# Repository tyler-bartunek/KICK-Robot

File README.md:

# The KICK Robot 

&nbsp;
&nbsp;
_Democratizing robotics, one shoebox at a time_

The KICK (Kinematically Interchangeable Control Kit) Robot framework is an open-source platform designed to make learning about and development of mobile robotic systems accessible, modular, and affordable.

## Table of Contents
- [Repository Structure](#repository-structure)
- [The Wiki](#the-wiki)
- [Module Descriptions](#module-descriptions)
- [Hardware](#hardware)
  - [Printed Components and Module Fit](#printed-components-and-module-fit)
- [Future development](#future-development)
- [FAQ](#faq)
- [License](#license)

## Repository Structure
- `/hardware/` – STL and STEP files for 3D printing
- `/software/` – Code for the centralized controller (in progress), example firmware for modules, and hardware test scripts
- `/docs/` – Printing instructions, and additional reference material as it becomes available (PDF)
- `/images/` – Holds images used in this README, as well as some others throughout the repository
- `README.md` – You are here.

## The Wiki
Documentation for this project, including: 

- Part orientation and printer setting recommendations
- Assembly instructions
- Calibration and hardware validation protocols
- System-level descriptions
- and more

are being migrated to the [project wiki](https://www.github.com/tyler-bartunek/KICK-Robot/wiki) for ease of access
and navigation purposes. There's a lot that goes into this system, and it is only fitting that worthy documentation
would be quite extensive, requiring a wiki to track it all. 

## Module Descriptions
Here are a few of the modules under development at present for the KICK Robot. Once these modules are fully fleshed
out, a homebrew guide will be produced and added to the wiki.

1. Wheels: This module consists of DC motors and mecanum wheels, represents minimal functional example (systems integration in process).
2. Shoeshine: Offers quadrupedal motion through use of servomotors (Pending Initial Design)
3. HexaBox: Requires six mounts, offers six-legged locomotion through use of servomotors. (Pending Initial Design)

Note that each module type gets its own uint8_t identifier. Here are some urrently used ID's within KICK framework:

| ID | Module Type |
|----|-------------|
|0x00 | **Reserved**: No Connection |
|0x01 | Echo test functionality |
|0x02 | Mecanum Wheel Version A |
|0x03 | Mecanum Wheel Version B |
|0x04 | Quadruped Leg Version A |
|0x05 | Quadruped Leg Version B |

## Hardware

### Printed Components and Module Fit
Both STEP and STL files for all components to be printed are provided under the hardware directory, with directions for
the base hardware and wheels module provided in the wiki. As modules are added, printing directions specific
to those modules will be added. This system was prototyped using an Ender 3 V2 and Cura slicer using 
PLA+, with dimensions set to reflect typical tolerances for that printer with the intent of clearance fits with minimal play between 
mounting rails and modules.

## Software
Files for characterizing your specific motors and verifying basic hardware connections to the Pi, such as the ADC for 
battery level monitoring and custom SPI fanout board PCB, are provided within this repository, as well as the base
code for the picos/modules. Module code was developed using the Raspberry Pi Pico C++ SDK and uses CMake (C++17).

ROS code for the Raspberry Pi was developed using the ros:jazzy-core docker image, and is available on a [separate repository](https://github.com/tyler-bartunek/kick_pi) for direct download on your raspberry pi once finished. Raspberry 3b+ or better strongly encouraged, as the project was developed on a 3b+. 

### Philosophy, Parent Classes: Validation Ongoing, wiki articles available upon completion
While this is explained in greater detail in the [wiki](https://www.github.com/tyler-bartunek/KICK-Robot/wiki), provided here is a brief overview
for integration purposes. Overall, the goal is for users to be able to extend this framework to arbitrary module configurations. 

#### Configuration Class (ROS)
Within this project's underlay (not to be confused with the ROS underlay), there is a kickbrain package. This package has a nested package within it
called "configuration_files". The Configuration class is defined within this subpackage, and all kinematic calculations are predicated on the geometry_msgs.msg.Twist message type coming from the motion planner, with these velocities defined relative to the center of mass, presumed or actual. 

**All user-defined configurations must inherit from the Configuration parent class and have both a fetch_commands and compute_received method defined as following signatures:** 
```
def fetch_commands(self, vel_cmd: Twist, feedback) -> list:
```

This method takes the center of mass velocity command from the motion planning node, which uses the built-in geometry\_msgs.Twist topic message type and any feedback to compute new actuator commands. 

``` 
def compute_received(self, device_data) -> Twist:
```
This method takes the data received from the bus\_hub node and computes the forward kinematics for your configuration to build feedback. 

Once you have your configuration kinematics defined, you go to the \_\_init\_\_.py file within the configuration\_files directory and add the frozenset of module ids that can be used to recognize your configuration. Note that it does use a frozenset, so if you need X number of modules for a successful deployment, be sure to add that check to your custom configuration's class definition.

__**Note that 0x00 is reserved as the "no connection" module ID, so your frozenset will need to include it if any connection points on the harness are disconnected**__

_There is a possibility that you will need to modify it directly within the kickbot_node package and rebuild it using colcon build --packages-select to achieve desired behavior, but efforts will be made to allow you to develop your own configuration definitions in an overlay._

#### Module Class (Pico)
The microcontroller code for the picos is organized in the following folder structure:

1. kick_pico: **project root, make/build from here** <br>
   a. modules: Contains the Module parent class and any subclass definition cpp and h files <br>
   b. utils: Additional cpp and header files for achieving any functionality the modules require, such as SPI communication or quadrature encoder reading <br>
   c. main.cpp: driver script, creates the `pico_device` instance and calls its `run()` method repeatedly <br>

You define your custom module by adding a header and cpp file within the modules subdirectory, and be sure to add the relevant files to the CMakeLists.txt file within that subdirectory. The custom module class that you define **must** inherit from the Module base class, and must include a run method override that defines your module's behavior in response to received data from the Pi. That run method **must** call `this -> Transfer(data)`, where `data` is a short (uint16\_t) being sent back to the pi. 

Minimally viable example of a custom subclass header file:
```
#pragma once

#include "Module.h"

class MinimalExample : public Module {
    
    public:
        
        MinimalExample();

        void run() override;

        ~MinimalExample() = default;
};
```

If your module requires additional custom header files to function, these go under the utils subdirectory and you will in turn need to modify that CMakeLists.txt file.

For example, if you need to add something for the module to read an encoder that you've either written or cloned a library for named MyReallyCoolEncLib, you would modify the very first line of CMakeLists.txt file in utils to read:

```
add_library(utils STATIC SPITools.cpp MyReallyCoolEncLib.cpp)
```

assuming that your library has a cpp file defined for it.

Lastly, you modify line 18 of main.cpp to have the name of your new module type

```
#define MODULE_TYPE MinimalExample
```

**When you define your own module definitions they must inherit from the Module base class, have a unique uint8_t ID defined, and contain a run() method override.** A sync_callback() method override is optional, but recommended if the modules need to act in a coordinated fashion (as most do). Wiki article coming soon.  

## Future development
This project is still under development, and additional details such as synchronization and timing
requirements will be made available as they are validated. Current work is focused on validating the ROS setup and getting the Wheels Module ready to ``roll". 

## FAQ

1. Why shoeboxes?

>I had originally set out to make what essentially amounts to just the wheels module as a CAD and mechatronic portfolio piece.
Seeking to understand the design considerations, I started to immerse myself in literature surrounding mecanum wheel devices 
and discovered something that is in hindsight self-evident: different design decisions like the wheel spacing and orientation 
fundamentally alters the dynamics of the system and therefore influence control. Creating modular systems to explore the impact 
of these parameters was largely underexplored in what I found, so I set out to make my own. But I needed a good frame. Something
cheap and easy to deploy. As I looked around me, I saw an unused shoebox. And the KICK Robot was born. 

>Realistically any cardboard box will work, but at the time a shoebox seemed like the right size for what I set out to accomplish.

2. Why didn't you use \<insert fastener here\> to fasten the modules to the box?

>In the early days, I explored a number of different means for mounting the hardware to the box. The current design for mounting
hardware to the box solves two problems simultaneously: the first is that of establishing a secure connection with minimal
assembly complexity, the second is offering a path for routing the wires from inside the box to the modules on the outside.

3. Doesn't the act of cutting into the box limit the reusability of a single box to test multiple design parameters?

>Yes, as do other adhesives that have enough strength to reliably anchor the hardware to the outside of the box. 

## License
As of 19 November, 2025, this project is licensed under the terms of the [Apache License-2.0](LICENSE). Software provided prior 
to this date was licensed under the terms of the MIT license, and includes the content of the directory 
`/software/Hardware Characterization/Wheels Module`. The transition to the Apache License-2.0 is to reflect that this repository
contains more than just software. 

This project also uses PyMC in the motor characterization code for the Wheels module. PyMC is also licensed under the terms
of the [Apache License-2.0](LICENSE), and also includes software licensed under the MIT license. A notice is provided in the
main directory of this repository, to underline this point and include the necessary copy of the MIT license for portions 
covered by that license.

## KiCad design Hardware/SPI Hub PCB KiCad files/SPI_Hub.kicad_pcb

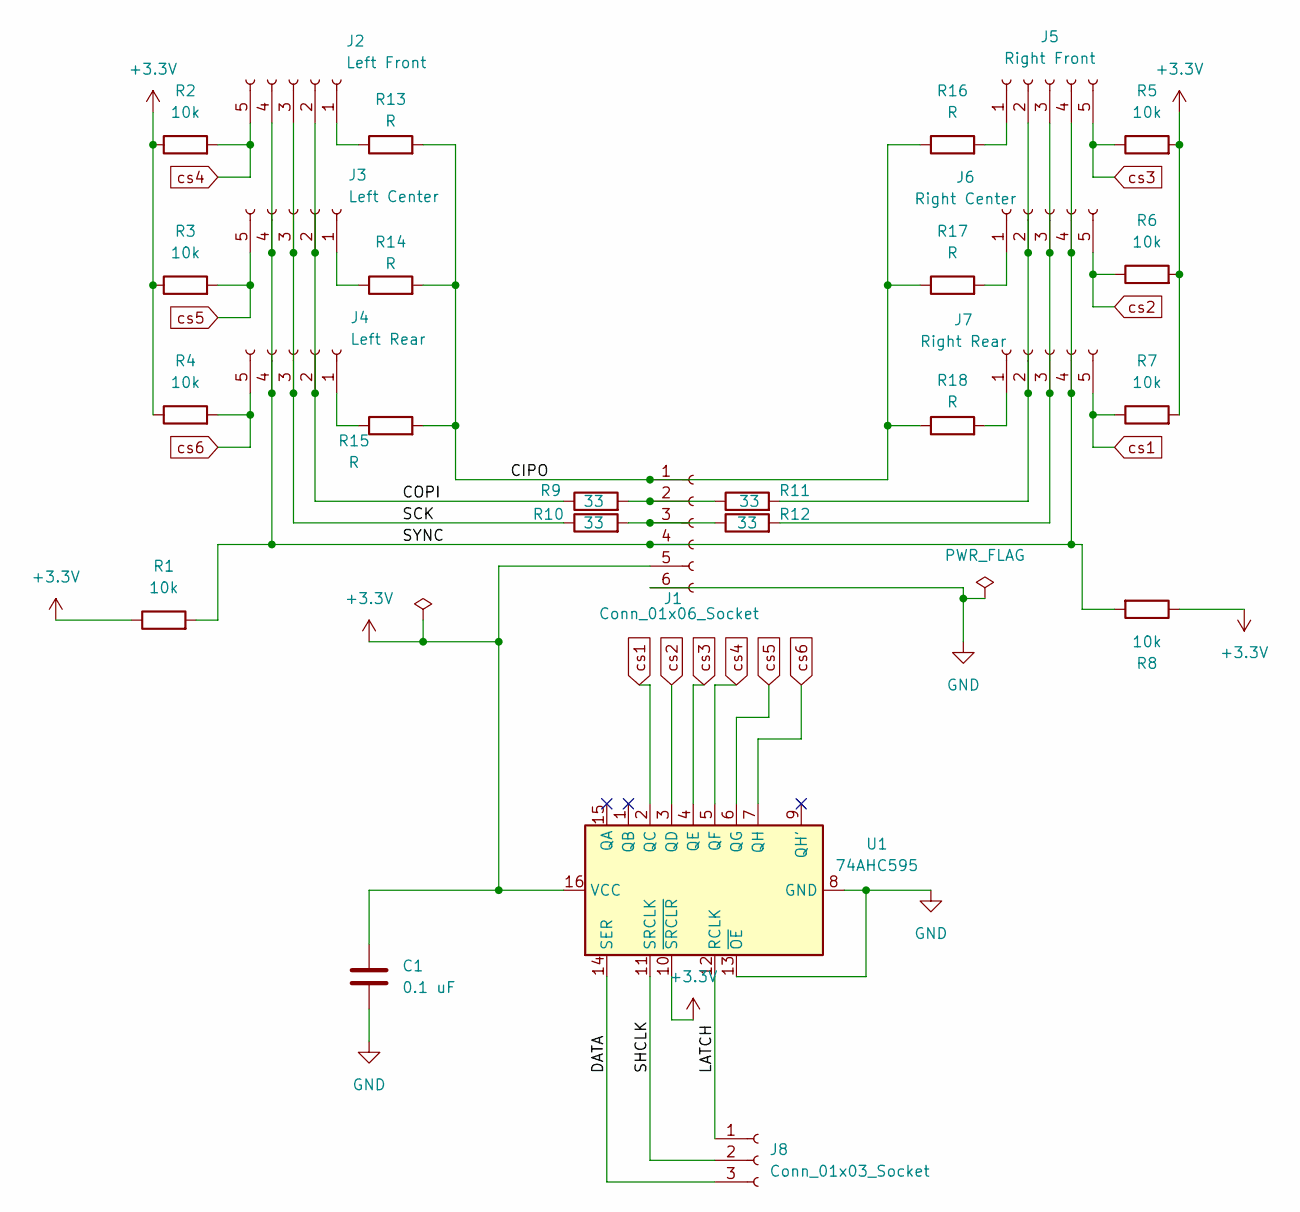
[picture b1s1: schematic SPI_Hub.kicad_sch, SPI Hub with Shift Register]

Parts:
C1: 0.1 uF; C_0805_2012Metric_Pad1.18x1.45mm_HandSolder
J1: Conn_01x06_Socket; JST_XH_B6B-XH-A_1x06_P2.50mm_Vertical
J2: Left Front; JST_XH_B5B-XH-A_1x05_P2.50mm_Vertical
J3: Left Center; JST_XH_B5B-XH-A_1x05_P2.50mm_Vertical
J4: Left Rear; JST_XH_B5B-XH-A_1x05_P2.50mm_Vertical
J5: Right Front; JST_XH_B5B-XH-A_1x05_P2.50mm_Vertical
J6: Right Center; JST_XH_B5B-XH-A_1x05_P2.50mm_Vertical
J7: Right Rear; JST_XH_B5B-XH-A_1x05_P2.50mm_Vertical
J8: Conn_01x03_Socket; JST_XH_B3B-XH-A_1x03_P2.50mm_Vertical
R1, R2, R3, R4, R5, R6, R7, R8: 10k; R_0805_2012Metric_Pad1.20x1.40mm_HandSolder
R9, R10, R11, R12: 33; R_0805_2012Metric_Pad1.20x1.40mm_HandSolder
R13, R14, R15, R16, R17, R18: R; R_0805_2012Metric_Pad1.20x1.40mm_HandSolder
U1: 74AHC595; DIP-16_W7.62mm_Socket

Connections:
+3.3V: C1.1, J1.5, R1.1, R2.1, R3.1, R4.1, R5.2, R6.2, R7.2, R8.1, U1.10 (~SRCLR), U1.16 (VCC)
/CIPO: J1.1, R13.2, R14.2, R15.2, R16.1, R17.1, R18.1
/COPI: J2.2, J3.2, J4.2, R9.1
/DATA: J8.3, U1.14 (SER)
/LATCH: J8.1, U1.12 (RCLK)
/SCK: J2.3, J3.3, J4.3, R10.1
/SHCLK: J8.2, U1.11 (SRCLK)
/SYNC: J1.4, J2.4, J3.4, J4.4, J5.4, J6.4, J7.4, R1.2, R8.2
GND: C1.2, J1.6, U1.8 (GND), U1.13 (~OE)
unnamed: J1.2, R9.2, R11.1
unnamed: J1.3, R10.2, R12.1
unnamed: J2.1, R13.1
unnamed: J3.1, R14.1
unnamed: J4.1, R15.1
unnamed: J5.1, R16.2
unnamed: J5.2, J6.2, J7.2, R11.2
unnamed: J5.3, J6.3, J7.3, R12.2
unnamed: J6.1, R17.2
unnamed: J7.1, R18.2
cs1: J7.5, R7.1, U1.2 (QC)
cs2: J6.5, R6.1, U1.3 (QD)
cs3: J5.5, R5.1, U1.4 (QE)
cs4: J2.5, R2.2, U1.5 (QF)
cs5: J3.5, R3.2, U1.6 (QG)
cs6: J4.5, R4.2, U1.7 (QH)

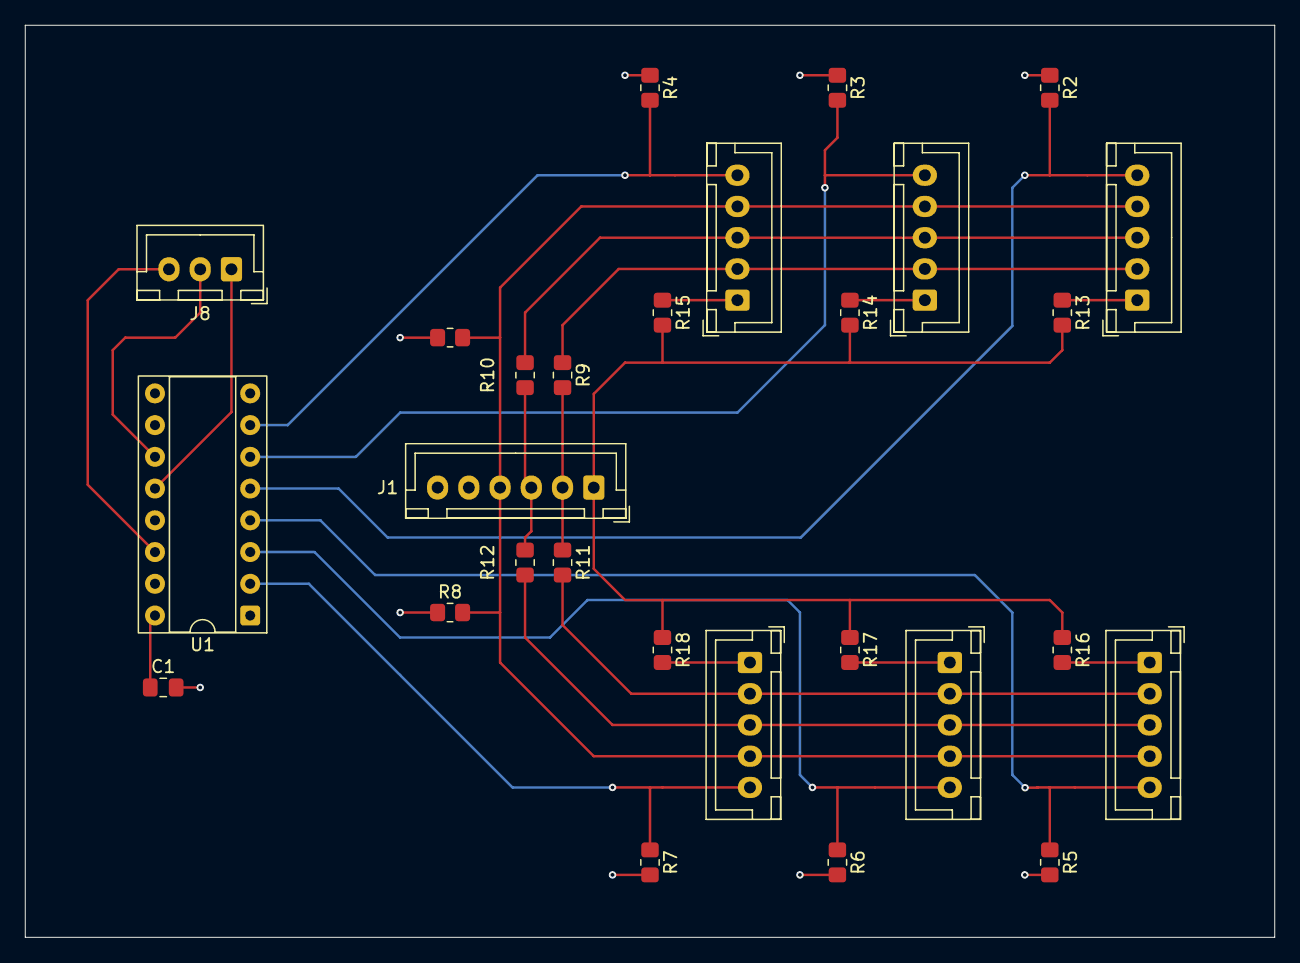
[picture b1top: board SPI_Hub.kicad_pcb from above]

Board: 4 copper layers, 100.0 x 73.0 mm, 28 parts (0 on the bottom side), 25 nets.

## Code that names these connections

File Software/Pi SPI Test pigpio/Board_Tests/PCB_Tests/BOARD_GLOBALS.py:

###PINS AND OTHER CONSTANTS

#SPI Pins
SPI0_SCLK = 11
CHANNEL = 0
CIPO = 9
COPI = 10
CS = 8 #Default CS for the SPI channel

SYNC_RATE = 32000

#Shift register pins
LATCH = 5 
DATA = 6
SHIFT_CLK = 13
OE = 26

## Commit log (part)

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2026-04-29 Enhance README with software and module class details
    Added sections on software, philosophy, and module class for better project documentation.
2026-04-29 Revise README for clarity on philosophy and classes
    Updated README to clarify philosophy and module structure.
2026-04-29 Updated README
    Updated the README to reflect changes in package structure and kinematic calculations.
2026-05-06 pico code syncs up with ros
2026-05-10 pico code passes echo test
2026-05-11 Update README with configuration method signatures
    Added method signatures for user-defined configurations in README.
2026-05-11 Enhance README with module ID details and setup guide
    Updated README to include module IDs and configuration instructions.
2026-06-01 Initial commit of desktop application
2026-06-02 Added more GUI skeleton
2026-06-04 Update Print Guide, GUI changes
2026-06-04 Initial Wheels commit
2026-06-05 toggle buttons and main stacked window added
2026-06-05 Add GUI components; include KICK logo
2026-06-08 Refactor MainWindow and RailCanvas; add SensorConfig and SLAM_Map widgets
2026-06-09 Add XML module and sensor definitions; update ControlWidget and MainWindow for new functionality
2026-06-09 Modified SensorConfig and RailCanvas to change settings windows based on xml file contents
2026-06-10 initial complete ros commit
2026-06-19 Add GUI Image. Refactor code structure for improved readability and maintainability
